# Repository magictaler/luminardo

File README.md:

Luminardo
=========

An open source Arduino-like hardware project with modular architecture and compact dimentions with the following features in base configuration:

- 8 digits by 6 segments VFD display;
- IR receiver;
- Photocell for brightness adjustmens;
- Buzzer;
- RGB LED with individual colors controlled independently by PWM;
- Single (either 5VDC or 12VDC) power supply;
- Lithium battery bucked up RTC;
- 1 Wire temperature sensor (with capability to connect more than one);
- USB Host functionality*;
- USB-to-Serial interface for progamming and debugging;
- 128 kb of program memory, 3.3V internal supply and logic levels;
- 5V tolerant ISP header; 
- I2C, secondary UART, secondary SPI for future extentions;
- PIR sensor;
- Integration with Arduino IDE;
- Firmware is tightly integrared with an awesome "Revision 2.0 of USB Host Library for Arduino" (thank you guys!)

for more information please visit http://luminardo.net and http://magictale.com

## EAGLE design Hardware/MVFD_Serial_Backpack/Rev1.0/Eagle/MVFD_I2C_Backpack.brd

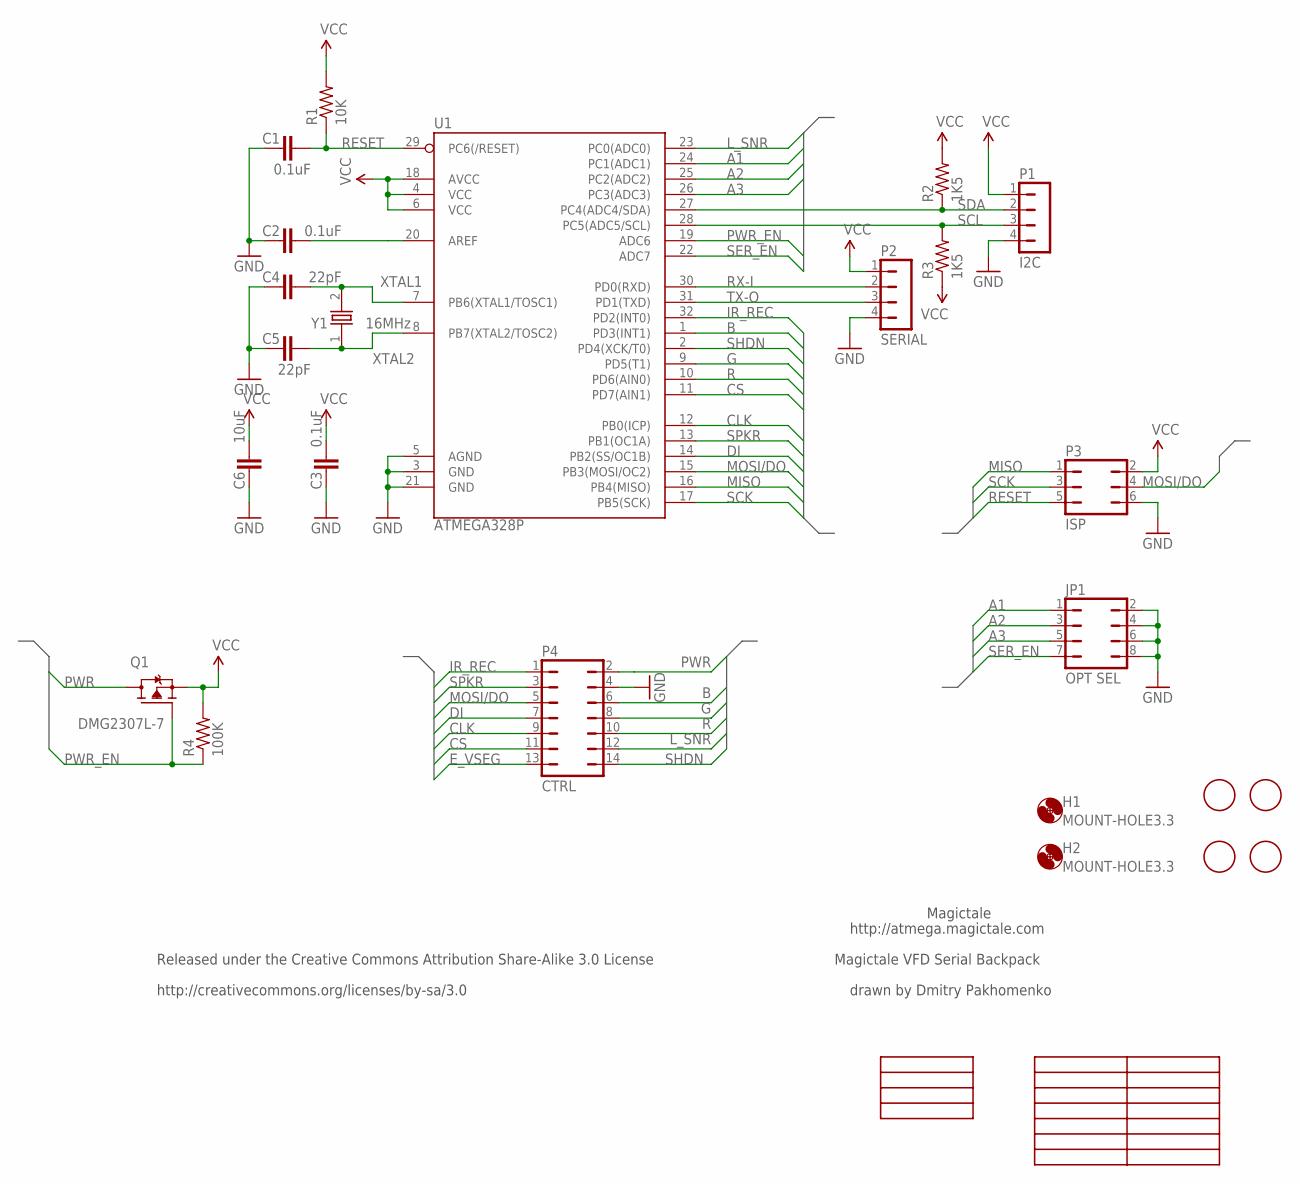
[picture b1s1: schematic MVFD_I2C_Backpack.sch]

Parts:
C1, C2, C3: 0.1uF; C1206; DIGIKEY 445-14296-1-ND
C4, C5: 22pF; C1206; DIGIKEY 399-8165-1-ND
C6: 10uF; C1206; DIGIKEY 399-1299-1-ND
FIDUTIAL1, FIDUTIAL2, FIDUTIAL3, FIDUTIAL4: FIDUCIAL; FIDUCIAL_1MM
H1, H2: MOUNT-HOLE3.3; 3,3
JP1: OPT SEL; CONN_HEADER_2X04; DIGIKEY 609-3226-ND
P1: I2C; CONN_HEADER_1X04_RA_POLAR; DIGIKEY 732-2701-ND
P2: SERIAL; CONN_HEADER_1X04_RA_POLAR; DIGIKEY 732-2701-ND
P3: ISP; CONN_HEADER_2X03; DIGIKEY 3M9459-ND
P4: CTRL; CONN_HEADER_2X07_F_MIRR; DIGIKEY S7075-ND
Q1: DMG2307L-7; SOT-23; DIGIKEY DMG2307L-7DICT-ND
R1: 10K; R1206; DIGIKEY RHM10KZCT-ND
R2, R3: 1K5; R1206; DIGIKEY RHM1.50KYCT-ND
R4: 100K; R1206; DIGIKEY RHM100KYCT-ND
U1: ATMEGA328P; TQFP32-08; DIGIKEY ATMEGA328P-AU-ND
U$1: MT_LOGO
U$2: HDR_7P2R_DESCR
U$4: JUMP_4X2_DESCR
Y1: 16MHz; HC-49U; DIGIKEY 887-1059-1-ND

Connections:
A1: JP1.1, U1.24 (PC1(ADC1))
A2: JP1.3, U1.25 (PC2(ADC2))
A3: JP1.5, U1.26 (PC3(ADC3))
AREF: C2.2, U1.20 (AREF)
B: P4.6, U1.1 (PD3(INT1))
CLK: P4.9, U1.12 (PB0(ICP))
CS: P4.11, U1.11 (PD7(AIN1))
DI: P4.7, U1.14 (PB2(SS/OC1B))
E_VSEG: P4.13
G: P4.8, U1.9 (PD5(T1))
GND: C1.1, C2.1, C3.1, C4.1, C5.1, C6.1, JP1.2, JP1.4, JP1.6, JP1.8, P1.4, P2.4, P3.6, P4.4, U1.3 (GND), U1.5 (AGND), U1.21 (GND)
IR_REC: P4.1, U1.32 (PD2(INT0))
L_SNR: P4.12, U1.23 (PC0(ADC0))
MISO: P3.1, U1.16 (PB4(MISO))
MOSI/DO: P3.4, P4.5, U1.15 (PB3(MOSI/OC2))
PWR: P4.2, Q1.3 (D)
PWR_EN: Q1.1 (G), R4.1, U1.19 (ADC6)
R: P4.10, U1.10 (PD6(AIN0))
RESET: C1.2, P3.5, R1.1, U1.29 (PC6(/RESET))
RX-I: P2.2, U1.30 (PD0(RXD))
SCK: P3.3, U1.17 (PB5(SCK))
SCL: P1.3, R3.2, U1.28 (PC5(ADC5/SCL))
SDA: P1.2, R2.1, U1.27 (PC4(ADC4/SDA))
SER_EN: JP1.7, U1.22 (ADC7)
SHDN: P4.14, U1.2 (PD4(XCK/T0))
SPKR: P4.3, U1.13 (PB1(OC1A))
TX-O: P2.3, U1.31 (PD1(TXD))
VCC: C3.2, C6.2, P1.1, P2.1, P3.2, Q1.2 (S), R1.2, R2.2, R3.1, R4.2, U1.4 (VCC), U1.6 (VCC), U1.18 (AVCC)
XTAL1: C4.2, U1.7 (PB6(XTAL1/TOSC1)), Y1.2
XTAL2: C5.2, U1.8 (PB7(XTAL2/TOSC2)), Y1.1

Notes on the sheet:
Magictale
http://atmega.magictale.com
Magictale VFD Serial Backpack
drawn by Dmitry Pakhomenko
Released under the Creative Commons Attribution Share-Alike 3.0 License
http://creativecommons.org/licenses/by-sa/3.0

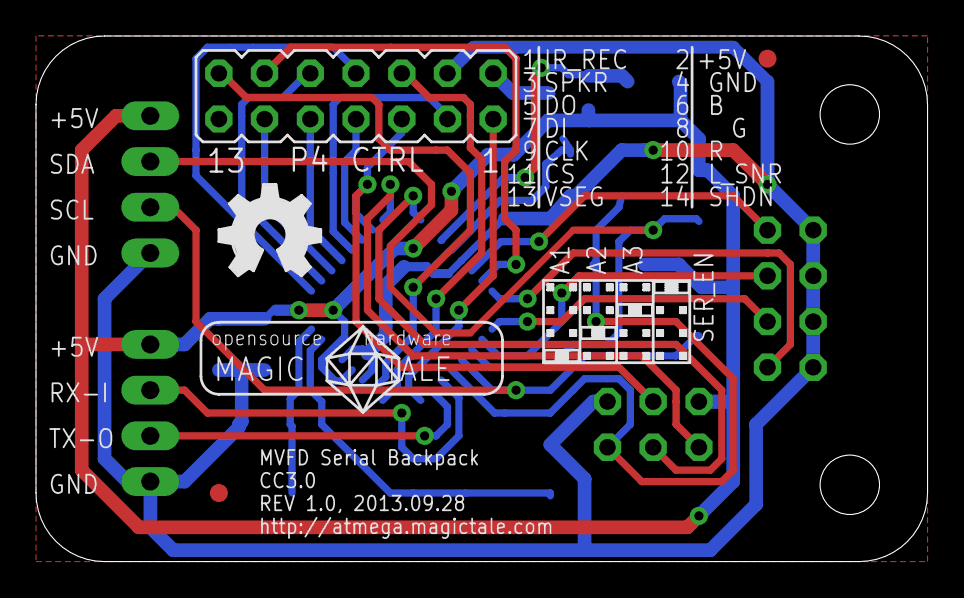
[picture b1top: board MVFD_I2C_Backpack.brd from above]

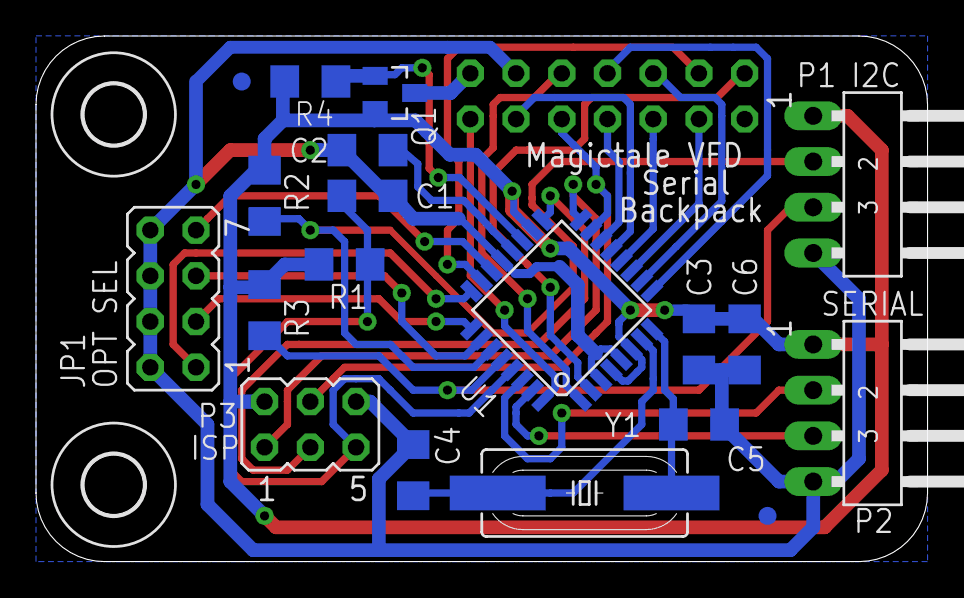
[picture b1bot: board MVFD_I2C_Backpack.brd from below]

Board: 2 copper layers, 49.5 x 29.2 mm, 28 parts (22 on the bottom side), 29 nets.

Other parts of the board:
U$3: LOGO_OSHW_FILLX200_NOTEXT

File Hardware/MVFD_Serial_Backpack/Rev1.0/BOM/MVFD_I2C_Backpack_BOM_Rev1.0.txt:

Partlist exported from D:/Projects/Electronics/InProgress/MVFD_I2C_Backpack/Eagle/Rev1.0/MVFD_I2C_Backpack.sch at 9/28/2013 10:06:53 PM

Qty Value          Device                   Package                   Parts                                      Description                                                             DIGIKEY           LICENSE OPT1 OPT2 OPT3 OPT4   P1     P2  P3   P4  P5 P6 P7 P8 P9  P10 P11 P12   P13  P14  PCBREV              PROJECT              URL                        
3   0.1uF          CAPACITOR_NPOL-1206      C1206                     C1, C2, C3                                 Non-Polarized capacitor in various packages                             445-14296-1-ND                                                                                                                                                                  
1   100K           RESISTOR-1206            R1206                     R4                                                                                                                 RHM100KYCT-ND                                                                                                                                                                   
1   10K            RESISTOR-1206            R1206                     R1                                                                                                                 RHM10KZCT-ND                                                                                                                                                                    
1   10uF           CAPACITOR_NPOL-1206      C1206                     C6                                         Non-Polarized capacitor in various packages                             399-1299-1-ND                                                                                                                                                                   
1   16MHz          OSC-XTAL-HC-49U-SMD      HC-49U                    Y1                                                                                                                 887-1059-1-ND                                                                                                                                                                   
2   1K5            RESISTOR-1206            R1206                     R2, R3                                                                                                             RHM1.50KYCT-ND                                                                                                                                                                  
2   22pF           CAPACITOR_NPOL-1206      C1206                     C4, C5                                     Non-Polarized capacitor in various packages                             399-8165-1-ND                                                                                                                                                                   
1   ATMEGA328P     ATMEGA168                TQFP32-08                 U1                                                                                                                 ATMEGA328P-AU-ND                                                                                                                                                                
1   CTRL           CONN_HEADER_2X07F_MIRR   CONN_HEADER_2X07_F_MIRR   P4                                         JUMPER                                                                  S7075-ND                                                                                                                                                                        
1   DMG2307L-7     TRANSISTOR_FET_TSM2301CX SOT-23                    Q1                                         20V P-Channel Enhancement Mode MOSFET                                   DMG2307L-7DICT-ND                                                                                                                                                               
4   FIDUCIAL       FIDUCIAL                 FIDUCIAL_1MM              FIDUTIAL1, FIDUTIAL2, FIDUTIAL3, FIDUTIAL4 For use by pick and place machines to calibrate the vision/machine, 1mm                                                                                                                                                                                 
1   HDR_7P2R_DESCR HDR_7P2R_DESCR           HDR_7P2R_DESCR            U$2                                                                                                                                                                IR_REC +5V SPKR GND DO B  DI G  CLK R   CS  L_SNR VSEG SHDN                                                                     
1   I2C            CONN_HEADER_1X04RA_POLAR CONN_HEADER_1X04_RA_POLAR P1                                         2.54 1x4 Header                                                         732-2701-ND                                                                                                                                                                     
1   ISP            CONN_HEADER_2X03         CONN_HEADER_2X03          P3                                         2.54 2x3 Header                                                         3M9459-ND                                                                                                                                                                       
1   JUMP_4X2_DESCR JUMP_4X2_DESCR           JUMP_4X2_DESCR            U$4                                                                                                                                          A1   A2   A3   SER_EN                                                                                                                                 
2   MOUNT-HOLE3.3  MOUNT-HOLE3.3            3,3                       H1, H2                                     MOUNTING HOLE with drill center marker                                                                                                                                                                                                                  
1   MT_LOGO        MT_LOGO                  MT_LOGO                   U$1                                                                                                                                  CC3.0                                                                                     REV 1.0, 2013.09.28 MVFD Serial Backpack http://atmega.magictale.com
1   OPT SEL        CONN_HEADER_2X04         CONN_HEADER_2X04          JP1                                        2.54 2x4 Header                                                         609-3226-ND                                                                                                                                                                     
1   SERIAL         CONN_HEADER_1X04RA_POLAR CONN_HEADER_1X04_RA_POLAR P2                                         2.54 1x4 Header                                                         732-2701-ND

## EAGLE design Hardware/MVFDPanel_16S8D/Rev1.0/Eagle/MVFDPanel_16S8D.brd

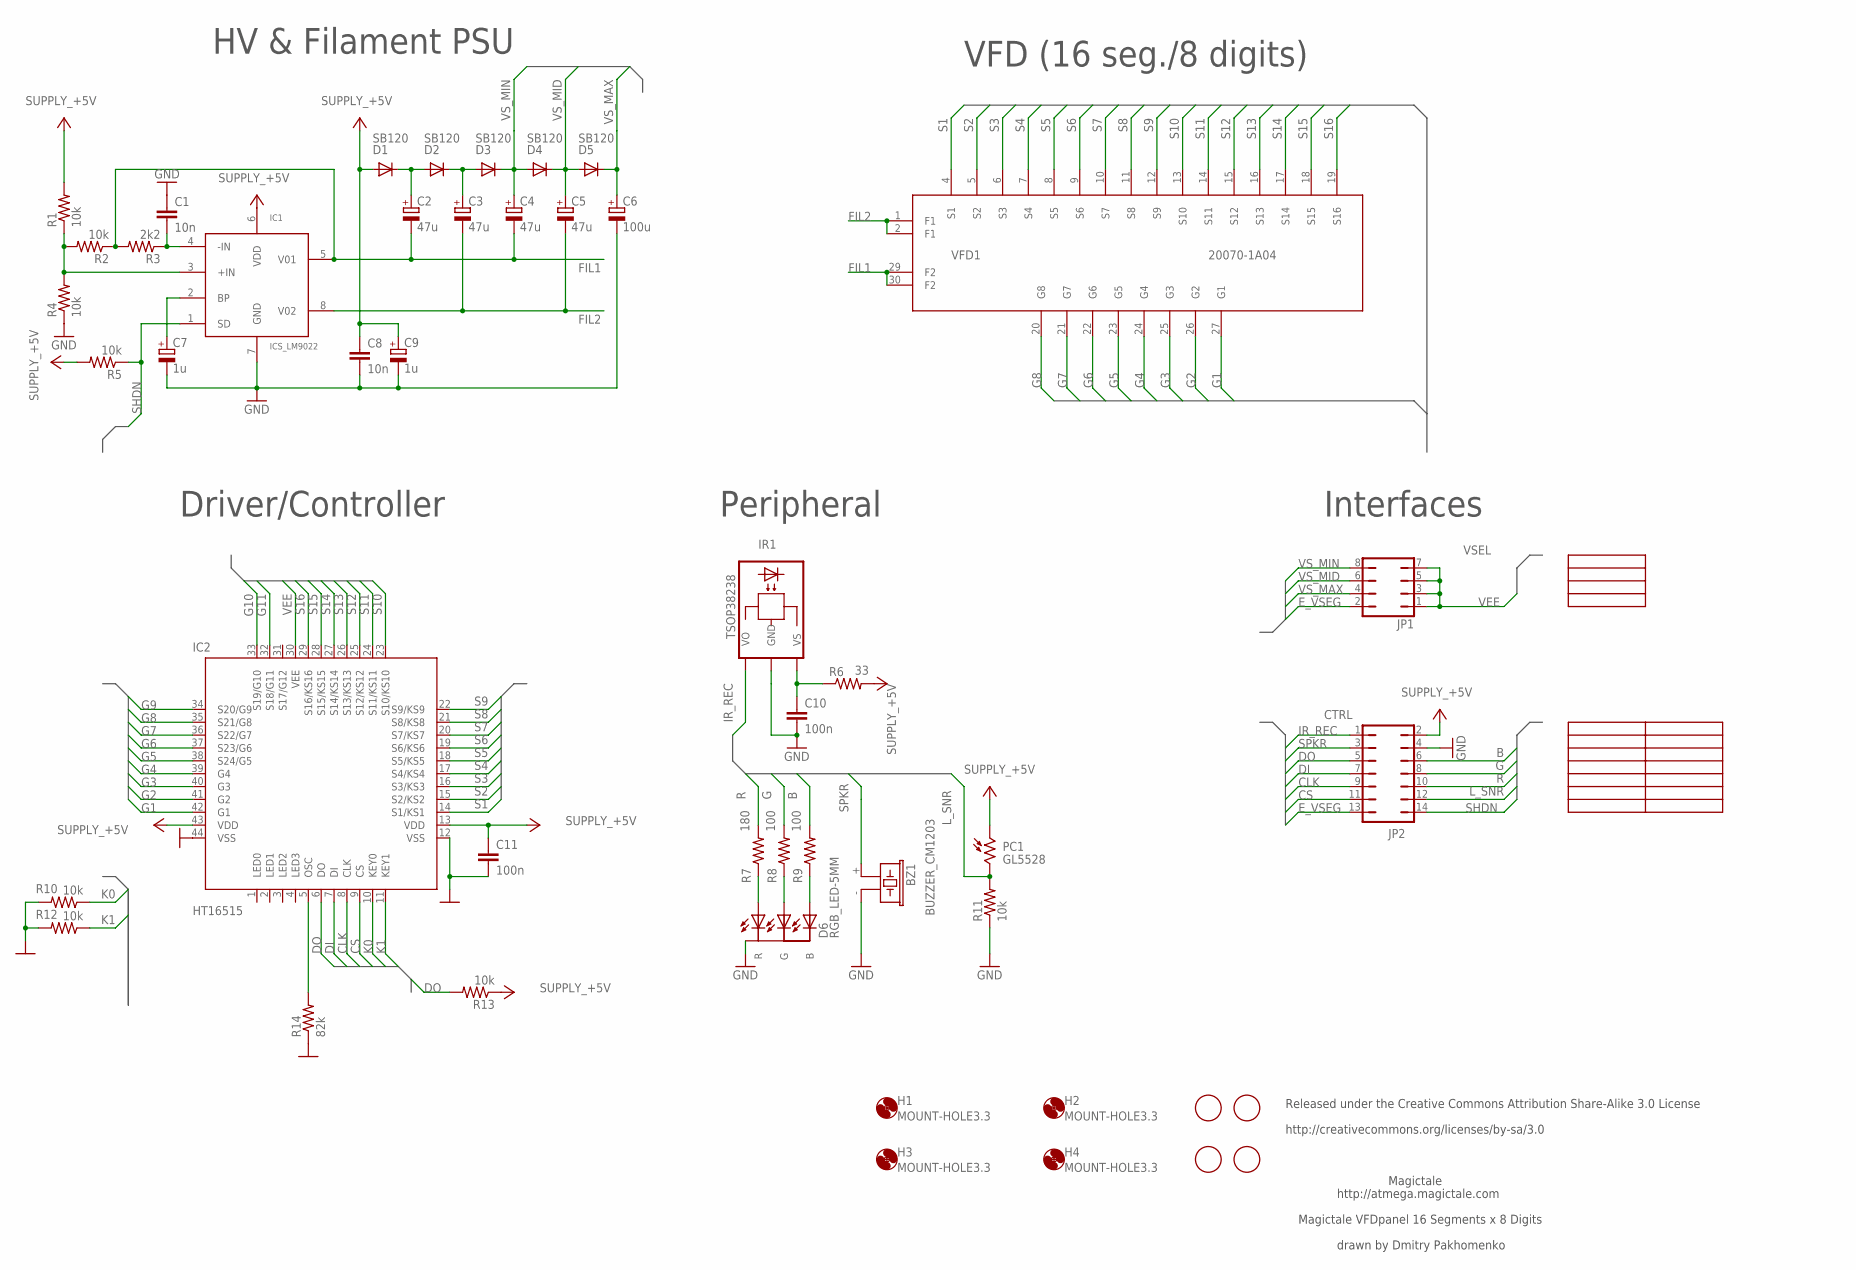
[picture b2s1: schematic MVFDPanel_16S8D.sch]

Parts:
BZ1: BUZZER_CM1203; CEM-1203
C1, C8: 10n; C025-025X050; DIGIKEY 399-4150-ND
C2, C3, C4, C5: 47u; E2,5-7; DIGIKEY P11232-ND
C6: 100u; E3,5-8; DIGIKEY P10294-ND
C7, C9: 1u; E2-5; DIGIKEY P13468-ND
C10, C11: 100n; C050-025X075; DIGIKEY 490-3859-ND
D1, D2, D3, D4, D5: SB120; DO41-10; DIGIKEY MBR160-ND
D6: RGB_LED-5MM
FIDUTIAL1, FIDUTIAL2, FIDUTIAL3, FIDUTIAL4: FIDUCIAL; FIDUCIAL_1MM
H1, H2, H3, H4: MOUNT-HOLE3.3; 3,3
IC1: ICS_LM9022; ICS_SOP08; DIGIKEY LM9022M-ND
IC2: HT16515; LQFP44-10X10
IR1: TSOP38238; DIGIKEY 751-1227-ND
JP1: VSEL; JP4Q
JP2: CTRL; JP7Q
PC1: GL5528
R1, R2, R4, R5, R10, R11, R12, R13: 10k; 0207/2V; DIGIKEY 10KQBK-ND
R3: 2k2; 0207/2V; DIGIKEY 2.2KQTR-ND
R6: 33; 0207/2V; DIGIKEY 33QBK-ND
R7: 180; 0207/2V; DIGIKEY 180QBK-ND
R8, R9: 100; 0207/2V; DIGIKEY 100QBK-ND
R14: 82k; 0207/2V; DIGIKEY 82KQBK-ND
U$1: MT_LOGO
U$2: HDR_7P2R_DESCR
U$3: JUMP_4X2_DESCR
VFD1: 20070-1A04

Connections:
+5V: C8.1, C9.+, C11.1, D1.A, IC1.6 (VDD), IC2.13 (VDD), IC2.43 (VDD), JP2.2, PC1.1, R1.2, R5.2, R6.2, R13.1
B: JP2.6, R9.2
CLK: IC2.8 (CLK), JP2.9
CS: IC2.9 (CS), JP2.11
DI: IC2.7 (DI), JP2.7
DO: IC2.6 (DO), JP2.5, R13.2
E_VSEG: JP1.2, JP2.13
FIL1: C2.-, C4.-, IC1.5 (V01), R2.1, R3.2, VFD1.29 (F2), VFD1.30 (F2)
FIL2: C3.-, C5.-, IC1.8 (V02), VFD1.1 (F1), VFD1.2 (F1)
G: JP2.8, R8.2
G1: IC2.42 (G1), VFD1.27 (G1)
G2: IC2.41 (G2), VFD1.26 (G2)
G3: IC2.40 (G3), VFD1.25 (G3)
G4: IC2.39 (G4), VFD1.24 (G4)
G5: IC2.38 (S24/G5), VFD1.23 (G5)
G6: IC2.37 (S23/G6), VFD1.22 (G6)
G7: IC2.36 (S22/G7), VFD1.21 (G7)
G8: IC2.35 (S21/G8), VFD1.20 (G8)
G9: IC2.34 (S20/G9)
G10: IC2.33 (S19/G10)
G11: IC2.32 (S18/G11)
GND: BZ1.- (2), C1.1, C6.-, C7.-, C8.2, C9.-, C10.2, C11.2, D6.CC, IC1.7 (GND), IC2.12 (VSS), IC2.44 (VSS), IR1.GND, JP2.4, R4.1, R10.2, R11.1, R12.2, R14.1
IR_REC: IR1.VO, JP2.1
K0: IC2.10 (KEY0), R10.1
K1: IC2.11 (KEY1), R12.1
L_SNR: JP2.12, PC1.2, R11.2
unnamed: C10.1, IR1.VS, R6.1
unnamed: IC2.5 (OSC), R14.2
unnamed: C7.+, IC1.2 (BP)
unnamed: D6.R, R7.1
unnamed: D6.G, R8.1
unnamed: D6.B, R9.1
unnamed: IC1.3 (+IN), R1.1, R2.2, R4.2
unnamed: C2.+, D1.C, D2.A
unnamed: C3.+, D2.C, D3.A
PORTD6: C1.2, IC1.4 (-IN), R3.1
R: JP2.10, R7.2
S1: IC2.14 (S1/KS1), VFD1.4 (S1)
S2: IC2.15 (S2/KS2), VFD1.5 (S2)
S3: IC2.16 (S3/KS3), VFD1.6 (S3)
S4: IC2.17 (S4/KS4), VFD1.7 (S4)
S5: IC2.18 (S5/KS5), VFD1.8 (S5)
S6: IC2.19 (S6/KS6), VFD1.9 (S6)
S7: IC2.20 (S7/KS7), VFD1.10 (S7)
S8: IC2.21 (S8/KS8), VFD1.11 (S8)
S9: IC2.22 (S9/KS9), VFD1.12 (S9)
S10: IC2.23 (S10/KS10), VFD1.13 (S10)
S11: IC2.24 (S11/KS11), VFD1.14 (S11)
S12: IC2.25 (S12/KS12), VFD1.15 (S12)
S13: IC2.26 (S13/KS13), VFD1.16 (S13)
S14: IC2.27 (S14/KS14), VFD1.17 (S14)
S15: IC2.28 (S15/KS15), VFD1.18 (S15)
S16: IC2.29 (S16/KS16), VFD1.19 (S16)
SHDN: IC1.1 (SD), JP2.14, R5.1
SPKR: BZ1.+ (1), JP2.3
VEE: IC2.30 (VEE), JP1.1, JP1.3, JP1.5, JP1.7
VS_MAX: C6.+, D5.C, JP1.4
VS_MID: C5.+, D4.C, D5.A, JP1.6
VS_MIN: C4.+, D3.C, D4.A, JP1.8

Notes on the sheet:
HV & Filament PSU
Driver/Controller
VFD (16 seg./8 digits)
Peripheral
Interfaces
Magictale
http://atmega.magictale.com
Magictale VFDpanel 16 Segments x 8 Digits
drawn by Dmitry Pakhomenko
Released under the Creative Commons Attribution Share-Alike 3.0 License
http://creativecommons.org/licenses/by-sa/3.0

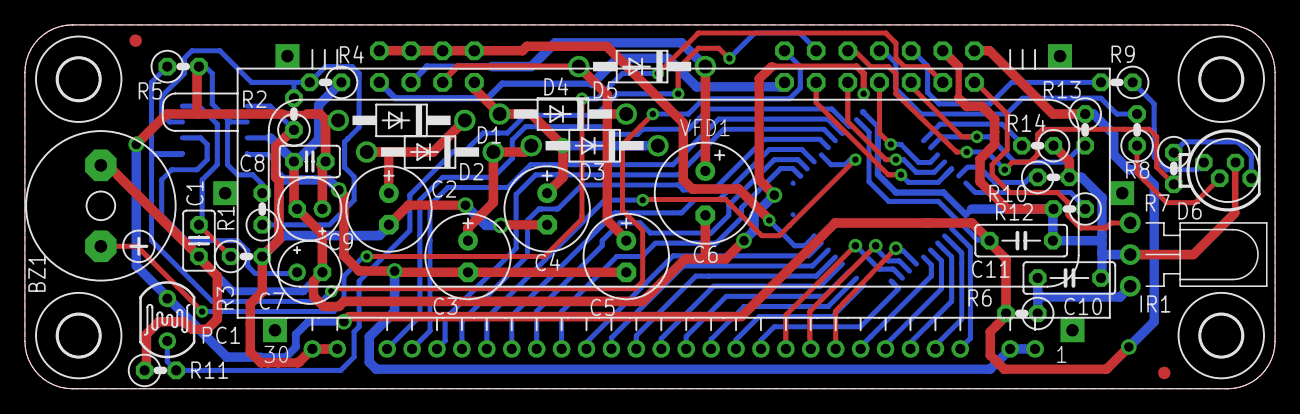
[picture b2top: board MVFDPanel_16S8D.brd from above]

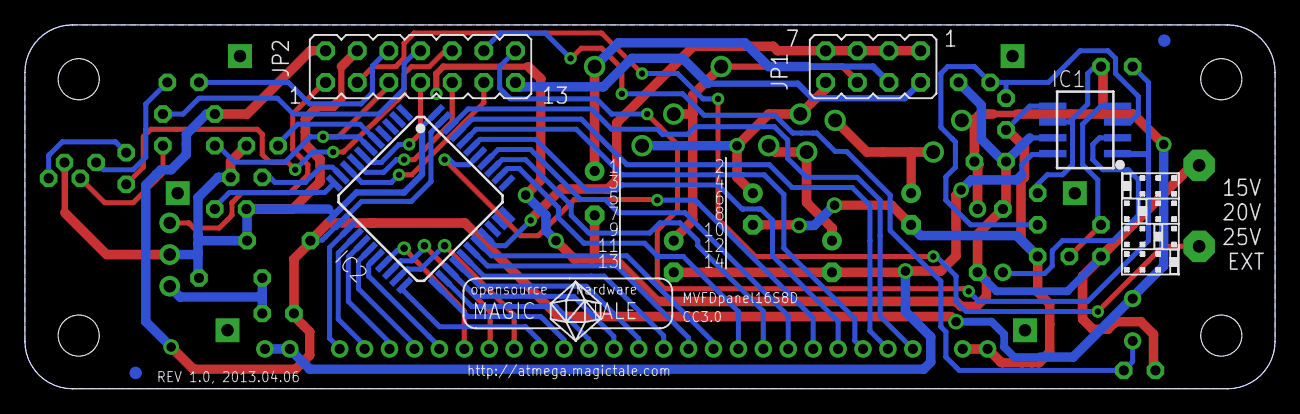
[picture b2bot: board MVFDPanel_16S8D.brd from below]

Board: 2 copper layers, 100.3 x 29.2 mm, 50 parts (9 on the bottom side), 56 nets.

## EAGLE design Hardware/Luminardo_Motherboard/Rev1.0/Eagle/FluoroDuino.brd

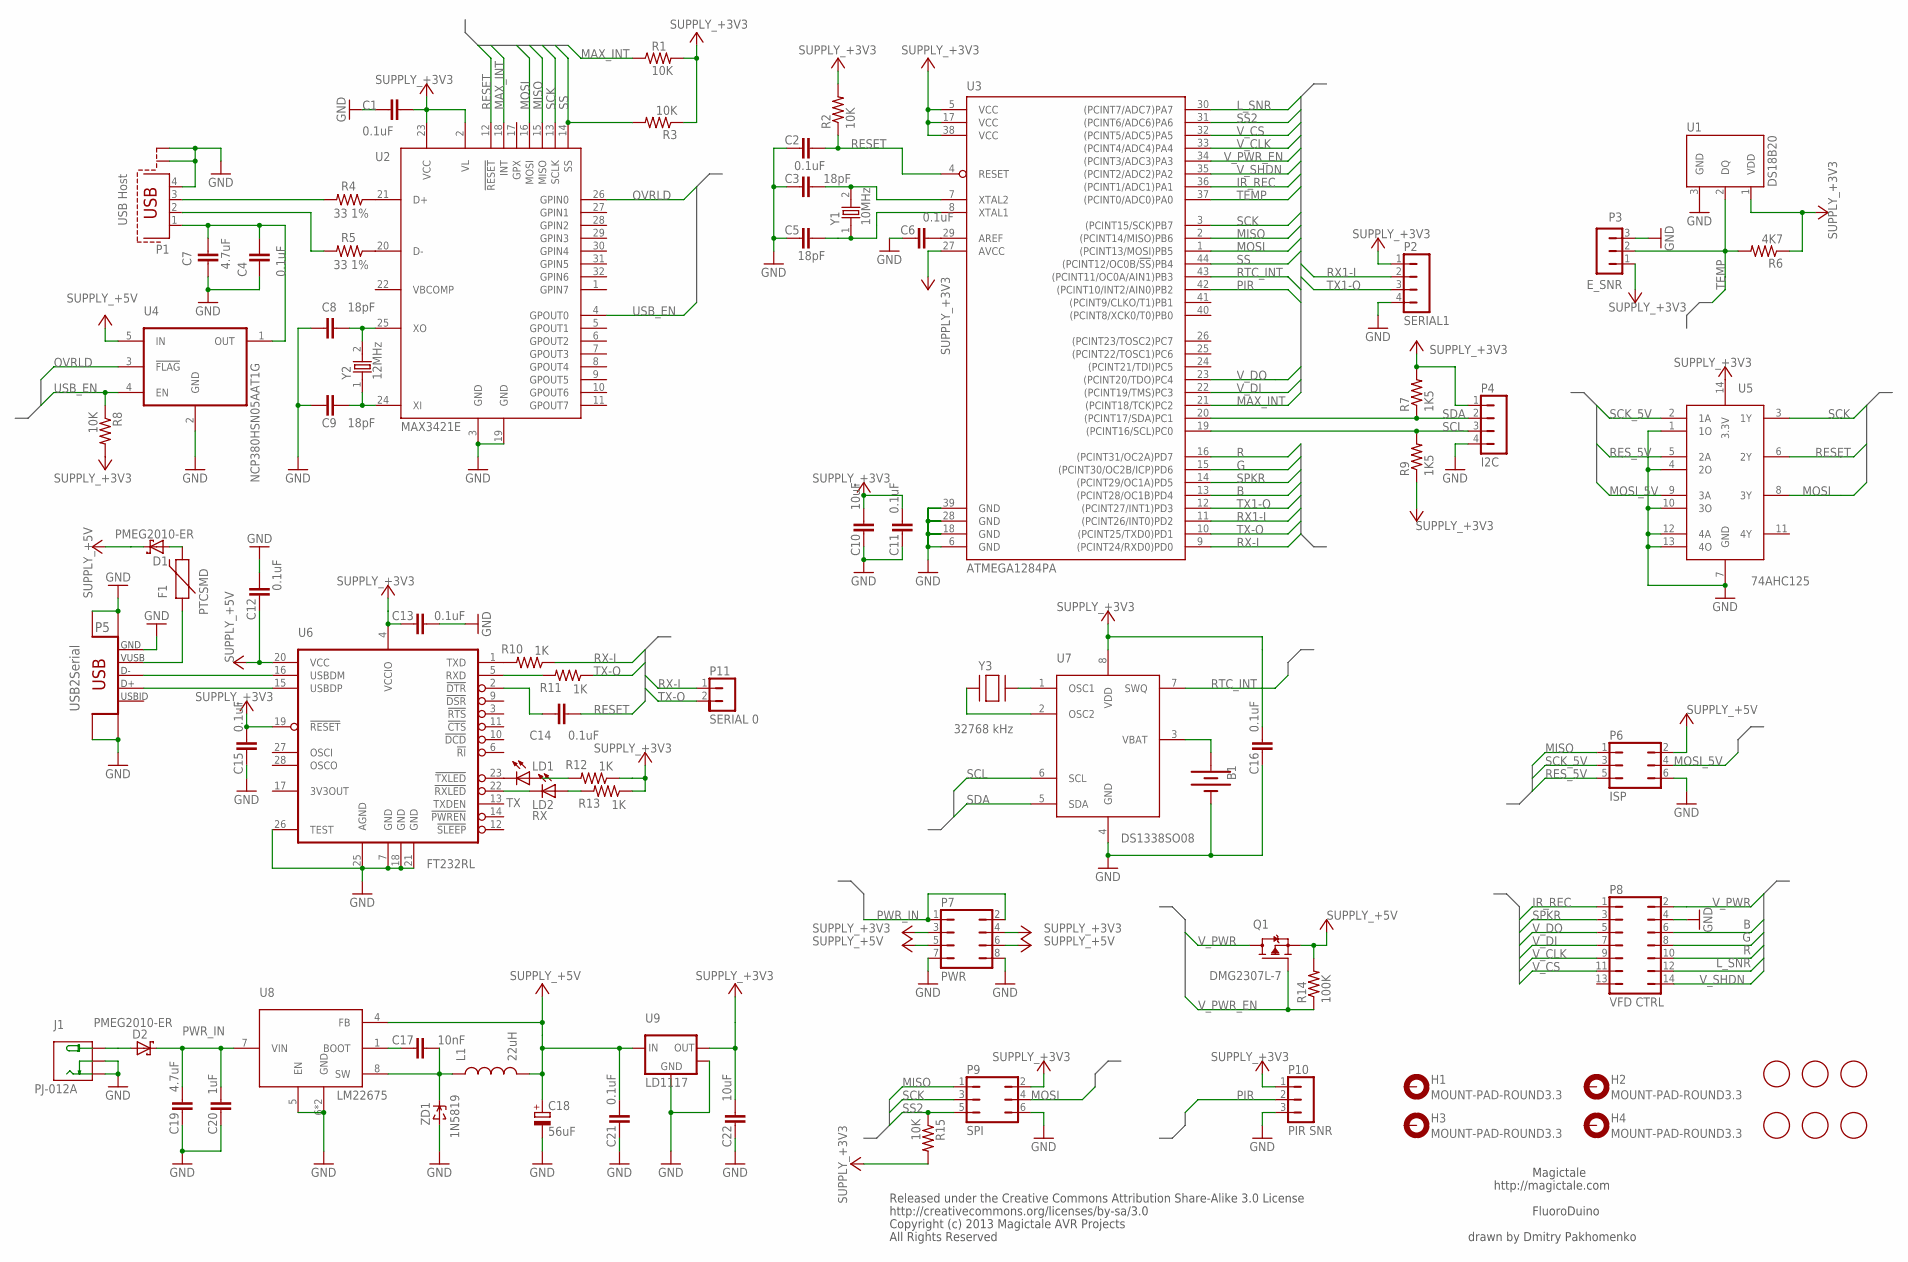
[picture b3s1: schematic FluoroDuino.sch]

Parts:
B1: BATTERY20PTH; BATTCOM_20MM_PTH; DIGIKEY BS-3-ND
C1, C2, C4, C6, C11, C12, C13, C14, C15, C16, C21: 0.1uF; C1206; DIGIKEY 445-14296-1-ND
C3, C5, C8, C9: 18pF; C1206; DIGIKEY 1276-1844-1-ND
C7, C19: 4.7uF; C1206; DIGIKEY 445-14685-1-ND
C10: 10uF; C1206; DIGIKEY 276-3044-1-ND
C17: 10nF; C1206; DIGIKEY 399-1234-1-ND
C18: 56uF; PANASONIC_C; DIGIKEY P16502CT-ND
C20: 1uF; C1206; DIGIKEY 587-1434-1-ND
C22: 10uF; C1206; DIGIKEY 1276-3044-1-ND
D1, D2: PMEG2010-ER; SOD123; DIGIKEY 568-6504-1-ND
F1: PTCSMD; PTC-1206; DIGIKEY 507-1798-1-ND
FIDUTIAL1, FIDUTIAL2, FIDUTIAL3, FIDUTIAL4, FIDUTIAL5, FIDUTIAL6: FIDUCIAL; FIDUCIAL_1MM
H1, H2, H3, H4: MOUNT-PAD-ROUND3.3; 3,3-PAD
J1: PJ-012A; DIGIKEY CP-012A-ND
L1: 22uH; VLC6045; DIGIKEY 445-6533-1-ND
LD1: TX; CHIPLED_1206; DIGIKEY 160-1737-1-ND
LD2: RX; CHIPLED_1206; DIGIKEY 160-1737-1-ND
P1: USB Host; USB-A-VER
P2: SERIAL1; CONN_HEADER_1X04; DIGIKEY SAM1034-02-ND
P3: E_SNR; CONN_HEADER_1X03; DIGIKEY SAM1034-02-ND
P4: I2C; CONN_HEADER_1X04; DIGIKEY SAM1034-02-ND
P5: USB2Serial; CONN_USB_MINI_RA; DIGIKEY 732-2735-ND
P6: ISP; CONN_HEADER_2X03; DIGIKEY 609-3210-ND
P7: PWR; CONN_HEADER_2X04; DIGIKEY 609-3235-ND
P8: VFD CTRL; CONN_HEADER_2X07_F_MIRR; DIGIKEY OR1103-ND
P9: SPI; CONN_HEADER_2X03; DIGIKEY 609-3210-ND
P10: PIR SNR; CONN_HEADER_1X03; DIGIKEY SAM1034-02-ND
P11: SERIAL 0; CONN_HEADER_1X02; DIGIKEY SAM1034-01-ND
Q1: DMG2307L-7; SOT-23; DIGIKEY DMG2307L-7DICT-ND
R1, R2, R3, R8, R15: 10K; R1206; DIGIKEY RMCF1206JT10K0CT-ND
R4, R5: 33 1%; R1206; DIGIKEY RMCF1206JT33R0
R6: 4K7; R1206; DIGIKEY RMCF1206JT4K70CT-ND
R7, R9: 1K5; R1206; DIGIKEY RNCP1206FTD1K50CT-ND
R10, R11, R12, R13: 1K; R1206; DIGIKEY RMCF1206JT1K00CT-ND
R14: 100K; R1206; DIGIKEY RMCF1206JT100KCT-ND
U1: DS18B20; TO-92-AMMO; DIGIKEY DS18B20+T&RCT-ND
U2: MAX3421E; TQFP32-08; DIGIKEY MAX3421EEHJ+-ND
U3: ATMEGA1284PA; TQFP44; DIGIKEY ATMEGA1284P-AURCT-ND
U4: NCP380HSN05AAT1G; SOT23-5; DIGIKEY NCP380HSN05AAT1GOSCT-ND
U5: 74AHC125; SO014; DIGIKEY 296-4530-1-ND
U6: FT232RL; SSOP-28; DIGIKEY 768-1007-1-ND
U7: DS1338SO08; SO08; DIGIKEY DS1338U-33+T&RCT-ND
U8: LM22675; SO08_POWER_PAD; DIGIKEY LM22675MR-5.0/NOPB-ND
U9: LD1117; SOT223; DIGIKEY 497-1241-1-ND
U$: MT_LOGOCOMPACT; MT_LOGO_COMPACT
Y1: 10MHz; XTAL_4X6; DIGIKEY 535-9833-1-ND
Y2: 12MHz; XTAL_4X6; DIGIKEY 535-9836-1-ND
Y3: 32768 kHz; XTAL3215; DIGIKEY 300-8816-1-ND
ZD1: 1N5819; SOD123; DIGIKEY 1N5819HW-FDICT-ND

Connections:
+3V3: C1.1, C10.2, C11.2, C13.1, C15.2, C16.2, C22.2, P2.1, P3.1, P4.1, P7.3, P7.4, P9.2, P10.1, R1.2, R2.2, R3.1, R6.1, R7.2, R8.2, R9.1, R12.1, R13.1, R15.2, U1.1 (VDD), U2.2 (VL), U2.23 (VCC), U3.5 (VCC), U3.17 (VCC), U3.27 (AVCC), U3.38 (VCC), U5.14 (3.3V), U6.4 (VCCIO), U6.19 (!RESET), U7.8 (VDD), U9.2 (OUT)
+5V: C12.1, C18.+, C21.2, D1.C, L1.2, P6.2, P7.5, P7.6, Q1.2 (S), R14.2, U4.5 (IN), U6.20 (VCC), U8.4 (FB), U9.3 (IN)
B: P8.6, U3.13 ((PCINT28/OC1B)PD4)
G: P8.8, U3.15 ((PCINT30/OC2B/ICP)PD6)
GND: B1.2 (-), C1.2, C2.1, C3.1, C4.2, C5.1, C6.1, C7.1, C8.1, C9.1, C10.1, C11.1, C12.2, C13.2, C15.1, C16.1, C18.-, C19.1, C20.1, C21.1, C22.1, J1.2, J1.3, P1.4, P1.S1, P1.S2, P2.4, P3.3, P4.4, P5.5 (GND), P5.S1 (BODY), P5.S2 (BODY), P5.S3 (BODY), P5.S4 (BODY), P6.6, P7.7, P7.8, P8.4, P9.6, P10.3, U1.3 (GND), U2.3 (GND), U2.19 (GND), U3.6 (GND), U3.18 (GND), U3.28 (GND), U3.39 (GND), U4.2 (GND), U5.1 (1O), U5.4 (2O), U5.7 (GND), U5.10 (3O), U5.12 (4A), U5.13 (4O), U6.7 (GND), U6.18 (GND), U6.21 (GND), U6.25 (AGND), U6.26 (TEST), U7.4 (GND), U8.5 (EN), U8.6 (GND), U8.BODY@1 (GND), U9.1 (GND), U9.4 (OUT), ZD1.A
IR_REC: P8.1, U3.36 ((PCINT1/ADC1)PA1)
L_SNR: P8.12, U3.30 ((PCINT7/ADC7)PA7)
MAX_INT: R1.1, U2.18 (INT), U3.21 ((PCINT18/TCK)PC2)
MISO: P6.1, P9.1, U2.15 (MISO), U3.2 ((PCINT14/MISO)PB6)
MOSI: P9.4, U2.16 (MOSI), U3.1 ((PCINT13/MOSI)PB5), U5.8 (3Y)
MOSI_5V: P6.4, U5.9 (3A)
unnamed: U7.1 (OSC1), Y3.P$2
unnamed: U7.2 (OSC2), Y3.P$1
unnamed: B1.1 (+), U7.3 (VBAT)
unnamed: P5.3 (D+), U6.15 (USBDP)
unnamed: P5.2 (D-), U6.16 (USBDM)
unnamed: D1.A, F1.2
unnamed: LD1.C, U6.23 (!TXLED)
unnamed: R11.2, U6.5 (RXD)
unnamed: R10.2, U6.1 (TXD)
unnamed: LD2.C, U6.22 (!RXLED)
unnamed: LD1.A, R12.2
unnamed: LD2.A, R13.2
unnamed: C14.2, U6.2 (!DTR)
unnamed: C9.2, U2.24 (XI), Y2.1
unnamed: C8.2, U2.25 (XO), Y2.2
unnamed: R4.1, U2.21 (D+)
unnamed: R5.1, U2.20 (D-)
unnamed: P1.3, R4.2
unnamed: P1.2, R5.2
unnamed: F1.1, P5.1 (VUSB)
unnamed: D2.A, J1.1
unnamed: C4.1, C7.2, P1.1, U4.1 (OUT)
unnamed: C17.1, U8.1 (BOOT)
unnamed: C6.2, U3.29 (AREF)
unnamed: C17.2, L1.1, U8.8 (SW), ZD1.C
OVRLD: U2.26 (GPIN0), U4.3 (!FLAG)
PIR: P10.2, U3.42 ((PCINT10/INT2/AIN0)PB2)
PWR_IN: C19.2, C20.2, D2.C, P7.1, P7.2, U8.7 (VIN)
R: P8.10, U3.16 ((PCINT31/OC2A)PD7)
RESET: C2.2, C14.1, R2.1, U2.12 (!RESET), U3.4 (RESET), U5.6 (2Y)
RES_5V: P6.5, U5.5 (2A)
RTC_INT: U3.43 ((PCINT11/OC0A/AIN1)PB3), U7.7 (SWQ)
RX1-I: P2.2, U3.11 ((PCINT26/INT0)PD2)
RX-I: P11.1, R10.1, U3.9 ((PCINT24/RXD0)PD0)
SCK: P9.3, U2.13 (SCLK), U3.3 ((PCINT15/SCK)PB7), U5.3 (1Y)
SCK_5V: P6.3, U5.2 (1A)
SCL: P4.3, R9.2, U3.19 ((PCINT16/SCL)PC0), U7.6 (SCL)
SDA: P4.2, R7.1, U3.20 ((PCINT17/SDA)PC1), U7.5 (SDA)
SPKR: P8.3, U3.14 ((PCINT29/OC1A)PD5)
SS: R3.2, U2.14 (SS), U3.44 ((PCINT12/OC0B/!SS!)PB4)
SS2: P9.5, R15.1, U3.31 ((PCINT6/ADC6)PA6)
TEMP: P3.2, R6.2, U1.2 (DQ), U3.37 ((PCINT0/ADC0)PA0)
TX1-O: P2.3, U3.12 ((PCINT27/INT1)PD3)
TX-O: P11.2, R11.1, U3.10 ((PCINT25/TXD0)PD1)
USB_EN: R8.1, U2.4 (GPOUT0), U4.4 (EN)
V_CLK: P8.9, U3.33 ((PCINT4/ADC4)PA4)
V_CS: P8.11, U3.32 ((PCINT5/ADC5)PA5)
V_DI: P8.7, U3.22 ((PCINT19/TMS)PC3)
V_DO: P8.5, U3.23 ((PCINT20/TDO)PC4)
V_PWR: P8.2, Q1.3 (D)
V_PWR_EN: Q1.1 (G), R14.1, U3.34 ((PCINT3/ADC3)PA3)
V_SHDN: P8.14, U3.35 ((PCINT2/ADC2)PA2)
XTAL1: C3.2, U3.7 (XTAL2), Y1.2
XTAL2: C5.2, U3.8 (XTAL1), Y1.1

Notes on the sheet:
Magictale
http://magictale.com
FluoroDuino
drawn by Dmitry Pakhomenko
Released under the Creative Commons Attribution Share-Alike 3.0 License
http://creativecommons.org/licenses/by-sa/3.0
Copyright (c) 2013 Magictale AVR Projects
All Rights Reserved

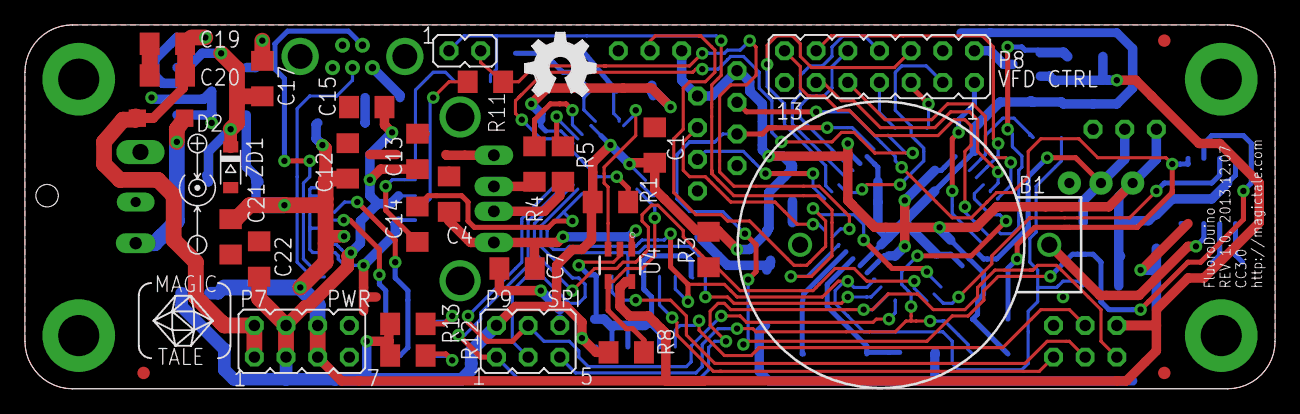
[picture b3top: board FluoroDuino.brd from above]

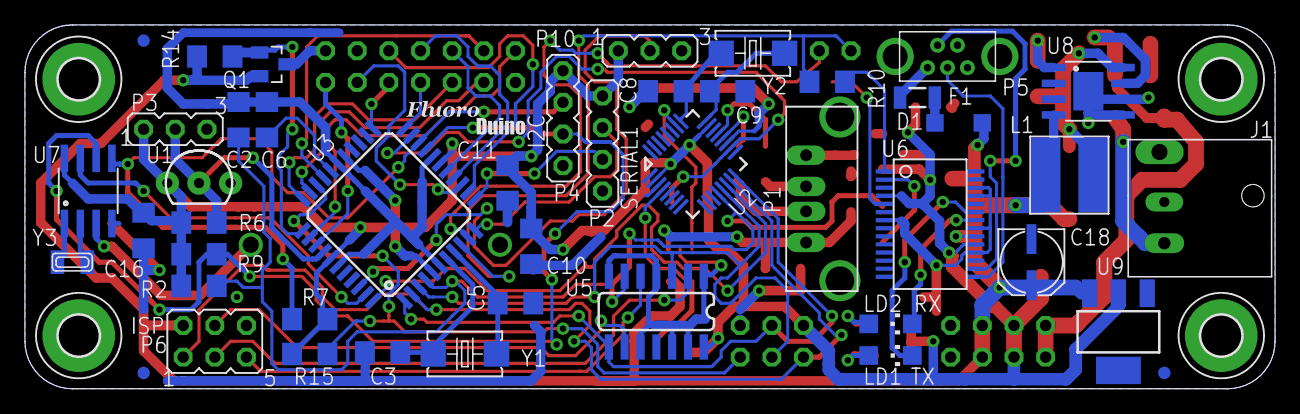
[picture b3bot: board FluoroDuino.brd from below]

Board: 2 copper layers, 100.3 x 29.2 mm, 83 parts (51 on the bottom side), 65 nets.

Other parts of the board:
U$1: FLUORODUINO_LOGO
U$3: LOGO_OSHW_FILLX200_NOTEXT

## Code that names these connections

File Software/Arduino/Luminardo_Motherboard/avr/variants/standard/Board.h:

#ifndef Board_h
#define Board_h

#if (LUMINARDO_REV) && (LUMINARDO_REV >= 2)
    #define RTC_INT_PIN		1	//PB1
    #define VFD_SPRK_PIN	3	//PB3
#else
    #define VFD_SPRK_PIN    	13 	//PD5
    #define RTC_INT_PIN		3	//PB3
#endif

#define TEMP_SNSR_PIN 		24	//PA0
#define VFD_CS_PIN   		29 	//PA5
#define VFD_SCLK_PIN 		28 	//PA4
#define VFD_DATAI_PIN 		19 	//PC3
#define VFD_DATAO_PIN 		20 	//PC4
#define VFD_SHDN_PIN    	26 	//PA2
#define VFD_R_PIN       	15 	//PD7
#define VFD_G_PIN       	14 	//PD6
#define VFD_B_PIN       	12 	//PD4

#define VFD_PWR_EN_PIN      	27 	//PA3
#define VFD_LIGHT_SNR_PIN    	31	//PA7
#define VFD_IR_REC_PIN		25	//PA1
#define SPI_SS2_PIN		30	//PA6
#define SPI_SCK_PIN		7	//PB7
#define SPI_MISO_PIN		6	//PB6
#define SPI_MOSI_PIN		5	//PB5
#define SPI_SS_PIN		4	//PB4

#define PIR_PIN			2	//PB2
#define MAX_INT_PIN		18	//PC2

#define FAILED_TEMPERATURE -999

enum enum_DsState
{
    dsIdle,
    dsTempConversion,
    dsInitDelay
};

#endif

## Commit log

2014-02-01 Initial commit
    Luminardo Rev 1.0
2014-02-01 Design files for MVFD panel and Backpack
    Design files for MVFD panel and serial backpack Rev.1.0
2014-02-02 Update README.md
    Hardware capabilities appended
2014-03-16 Typo in name fixed
    Typo in 'Luminardo' name - there was missing 'a'. No functional impact.
2014-03-23 #define LUMINARDO
    #define LUMINARDO is appended to Arduino.h
2016-06-25 Compatible with Arduino 1.6.9
    Restructuring to make it compatible with Arduino 1.6.9 IDE
2016-12-12 Luminardo Rev 2.0 - Michelle's clock
    Luminardo Rev 2.0 - Michelle's clock (with German resources)

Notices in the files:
parts and their libraries:
SparkFun-PowerIC: Licensing: CC v3.0 Share-Alike You are welcome to use this library for commercial purposes.
LICENSE: CC3.0
